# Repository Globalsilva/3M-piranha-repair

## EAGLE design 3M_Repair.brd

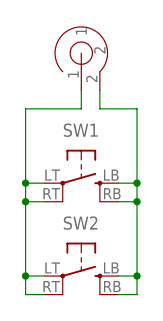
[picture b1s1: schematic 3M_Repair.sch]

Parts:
P1: 3M_PR
SW1: PUSH_BUTTON6X6; 6X6
SW2: PUSH_BUTTON12X12; 12X12

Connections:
unnamed: P1.2, SW1.LB, SW1.RB, SW2.LB, SW2.RB
unnamed: P1.1, SW1.LT, SW1.RT, SW2.LT, SW2.RT

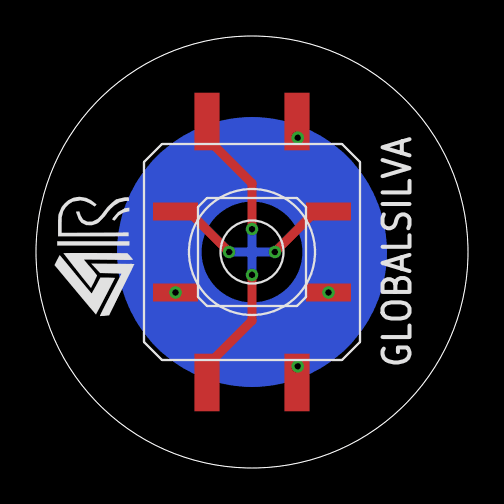
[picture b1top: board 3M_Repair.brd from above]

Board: 2 copper layers, 24.0 x 24.0 mm, 4 parts (1 on the bottom side), 2 nets.

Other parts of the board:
U$1: RAFAEL_SILVA_5MM_ALT_3

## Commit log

2019-10-21 "drawn boards"
2019-10-21 panel
